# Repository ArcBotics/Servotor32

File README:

All hardware for Servotor32 is licensed under a Creative Commons Attribution ShareAlike 3.0 United States License.
The full terms of this license can be read at:
http://creativecommons.org/licenses/by-sa/3.0/

All software is licensed under the MIT License.
Permission is hereby granted, free of charge, to any person obtaining a copy of this software and associated documentation files (the "Software"), to deal in the Software without restriction, including without limitation the rights to use, copy, modify, merge, publish, distribute, sublicense, and/or sell copies of the Software, and to permit persons to whom the Software is furnished to do so, subject to the following conditions:

The above copyright notice and this permission notice shall be included in all copies or substantial portions of the Software.

THE SOFTWARE IS PROVIDED "AS IS", WITHOUT WARRANTY OF ANY KIND, EXPRESS OR IMPLIED, INCLUDING BUT NOT LIMITED TO THE WARRANTIES OF MERCHANTABILITY, FITNESS FOR A PARTICULAR PURPOSE AND NONINFRINGEMENT. IN NO EVENT SHALL THE AUTHORS OR COPYRIGHT HOLDERS BE LIABLE FOR ANY CLAIM, DAMAGES OR OTHER LIABILITY, WHETHER IN AN ACTION OF CONTRACT, TORT OR OTHERWISE, ARISING FROM, OUT OF OR IN CONNECTION WITH THE SOFTWARE OR THE USE OR OTHER DEALINGS IN THE SOFTWARE.

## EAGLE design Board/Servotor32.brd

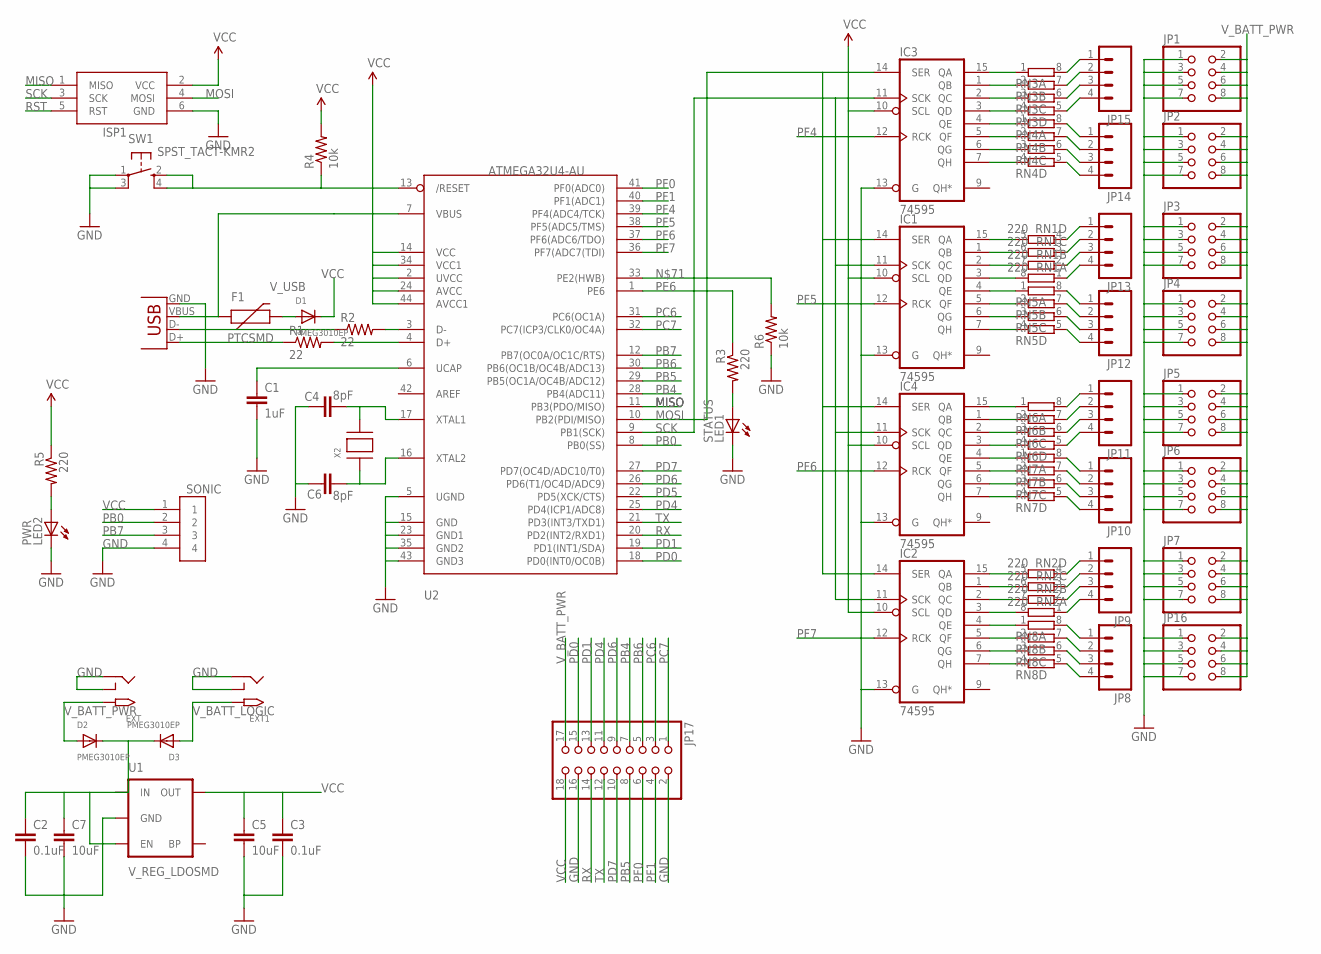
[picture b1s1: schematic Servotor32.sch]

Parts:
C1: 1uF; 0603-CAP
C2, C3: 0.1uF; 0603-CAP
C4, C6: 8pF; 0603-CAP
C5, C7: 10uF; 0805
D1, D2, D3: PMEG3010EP; SOD-128
EXT, EXT1: 2.1MMJACKTHM; PJ-102A
F1: PTCSMD; PTC-1206
IC1, IC2, IC3, IC4: 74595; TSSOP16
ISP1: AVRISP-6; AVRISP
JP1, JP2, JP3, JP4, JP5, JP6, JP7, JP16: PINHD-2X4; 2X04
JP8, JP9, JP10, JP11, JP12, JP13, JP14, JP15: M04PTH; 1X04
JP17: PINHD-2X9-BIG; 2X09-BIG
LED1: STATUS; SML0805
LED2: PWR; SML0805
R1, R2: 22; 0603-RES
R3, R5: 220; 0603-RES
R4, R6: 10k; 0603-RES
RN1, RN2: 220; EXB38V
RN3, RN4, RN5, RN6, RN7, RN8: 4R-NEXB38V; EXB38V
SONIC: SONIC; 1X04-BIG
SW1: SPST_TACT-KMR2; KMR2
U1: V_REG_LDOSMD; SOT23-5
U2: ATMEGA32U4-AU; TQFP44
X1: USBSMD; USB-MINIB
X2: XTALNX5032; NX5032

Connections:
D+: R1.2, U2.4 (D+)
D-: R2.2, U2.3 (D-)
GND: C1.2, C2.2, C3.2, C4.2, C5.2, C6.2, C7.2, EXT.RING, EXT.RING_SW, EXT1.RING, EXT1.RING_SW, IC1.8 (GND), IC1.13 (G), IC2.8 (GND), IC2.13 (G), IC3.8 (GND), IC3.13 (G), IC4.8 (GND), IC4.13 (G), ISP1.6 (GND), JP1.1, JP1.3, JP1.5, JP1.7, JP2.1, JP2.3, JP2.5, JP2.7, JP3.1, JP3.3, JP3.5, JP3.7, JP4.1, JP4.3, JP4.5, JP4.7, JP5.1, JP5.3, JP5.5, JP5.7, JP6.1, JP6.3, JP6.5, JP6.7, JP7.1, JP7.3, JP7.5, JP7.7, JP16.1, JP16.3, JP16.5, JP16.7, JP17.2, JP17.16, LED1.C, LED2.C, R6.1, SONIC.4, SW1.1, SW1.3 (P1), U1.2 (GND), U2.5 (UGND), U2.15 (GND), U2.23 (GND1), U2.35 (GND2), U2.43 (GND3), X1.GND
MISO: ISP1.1 (MISO), U2.11 (PB3(PDO/MISO))
MOSI: IC1.14 (SER), IC2.14 (SER), IC3.14 (SER), IC4.14 (SER), ISP1.4 (MOSI), U2.10 (PB2(PDI/MISO))
unnamed: IC3.15 (QA), RN3.1
unnamed: LED2.A, R5.2
unnamed: IC1.3 (QD), RN1.8 (2)
unnamed: R2.1, X1.D-
unnamed: R1.1, X1.D+
unnamed: IC2.3 (QD), RN2.8 (2)
unnamed: IC1.2 (QC), RN1.7 (2)
unnamed: IC2.2 (QC), RN2.7 (2)
unnamed: IC1.1 (QB), RN1.6 (2)
unnamed: IC3.1 (QB), RN3.2 (1)
unnamed: IC1.15 (QA), RN1.5 (2)
unnamed: IC3.2 (QC), RN3.3 (1)
unnamed: IC3.3 (QD), RN3.4 (1)
unnamed: IC2.1 (QB), RN2.6 (2)
unnamed: IC2.15 (QA), RN2.5 (2)
unnamed: IC3.4 (QE), RN4.1
unnamed: IC3.5 (QF), RN4.2 (1)
unnamed: IC3.6 (QG), RN4.3 (1)
unnamed: IC3.7 (QH), RN4.4 (1)
unnamed: IC1.4 (QE), RN5.1
unnamed: IC1.5 (QF), RN5.2 (1)
unnamed: JP13.1, RN1.4 (1)
unnamed: IC1.6 (QG), RN5.3 (1)
unnamed: IC1.7 (QH), RN5.4 (1)
unnamed: JP12.1, RN5.8 (2)
unnamed: JP13.2, RN1.3 (1)
unnamed: JP13.3, RN1.2 (1)
unnamed: JP13.4, RN1.1
unnamed: JP12.2, RN5.7 (2)
unnamed: JP12.3, RN5.6 (2)
unnamed: JP12.4, RN5.5 (2)
unnamed: JP15.1, RN3.8 (2)
unnamed: JP15.2, RN3.7 (2)
unnamed: JP15.3, RN3.6 (2)
unnamed: JP15.4, RN3.5 (2)
unnamed: JP14.1, RN4.8 (2)
unnamed: JP14.2, RN4.7 (2)
unnamed: JP14.3, RN4.6 (2)
unnamed: JP14.4, RN4.5 (2)
unnamed: JP9.4, RN2.1
unnamed: JP9.3, RN2.2 (1)
unnamed: JP9.2, RN2.3 (1)
unnamed: JP9.1, RN2.4 (1)
unnamed: IC2.4 (QE), RN8.1
unnamed: IC2.5 (QF), RN8.2 (1)
unnamed: IC2.6 (QG), RN8.3 (1)
unnamed: IC2.7 (QH), RN8.4 (1)
unnamed: JP8.1, RN8.8 (2)
unnamed: JP8.2, RN8.7 (2)
unnamed: JP8.3, RN8.6 (2)
unnamed: JP8.4, RN8.5 (2)
unnamed: IC4.1 (QB), RN6.2 (1)
unnamed: IC4.2 (QC), RN6.3 (1)
unnamed: IC4.3 (QD), RN6.4 (1)
unnamed: IC4.4 (QE), RN7.1
unnamed: IC4.5 (QF), RN7.2 (1)
unnamed: IC4.6 (QG), RN7.3 (1)
unnamed: IC4.7 (QH), RN7.4 (1)
unnamed: JP11.1, RN6.8 (2)
unnamed: JP11.2, RN6.7 (2)
unnamed: JP11.3, RN6.6 (2)
unnamed: JP11.4, RN6.5 (2)
unnamed: JP10.1, RN7.8 (2)
unnamed: JP10.2, RN7.7 (2)
unnamed: JP10.3, RN7.6 (2)
unnamed: JP10.4, RN7.5 (2)
unnamed: LED1.A, R3.2
unnamed: R6.2, U2.33 (PE2(HWB))
unnamed: IC4.15 (QA), RN6.1
PB0: SONIC.2, U2.8 (PB0(SS))
PB4: JP17.7, U2.28 (PB4(ADC11))
PB5: JP17.8, U2.29 (PB5(OC1A/OC4B/ADC12))
PB6: JP17.5, U2.30 (PB6(OC1B/OC4B/ADC13))
PB7: SONIC.3, U2.12 (PB7(OC0A/OC1C/RTS))
PC6: JP17.3, U2.31 (PC6(OC1A))
PC7: JP17.1, U2.32 (PC7(ICP3/CLK0/OC4A))
PD0: JP17.15, U2.18 (PD0(INT0/OC0B))
PD1: JP17.13, U2.19 (PD1(INT1/SDA))
PD4: JP17.11, U2.25 (PD4(ICP1/ADC8))
PD5: U2.22 (PD5(XCK/CTS))
PD6: JP17.9, U2.26 (PD6(T1/OC4D/ADC9))
PD7: JP17.10, U2.27 (PD7(OC4D/ADC10/T0))
PE6: R3.1, U2.1 (PE6)
PF0: JP17.6, U2.41 (PF0(ADC0))
PF1: JP17.4, U2.40 (PF1(ADC1))
PF4: IC3.12 (RCK), U2.39 (PF4(ADC4/TCK))
PF5: IC1.12 (RCK), U2.38 (PF5(ADC5/TMS))
PF6: IC4.12 (RCK), U2.37 (PF6(ADC6/TDO))
PF7: IC2.12 (RCK), U2.36 (PF7(ADC7(TDI))
RST: ISP1.5 (RST), R4.1, SW1.2 (S), SW1.4 (S1), U2.13 (/RESET)
RX: JP17.14, U2.20 (PD2(INT2/RXD1))
SCK: IC1.11 (SCK), IC2.11 (SCK), IC3.11 (SCK), IC4.11 (SCK), ISP1.3 (SCK), U2.9 (PB1(SCK))
TX: JP17.12, U2.21 (PD3(INT3/TXD1))
UCAP: C1.1, U2.6 (UCAP)
VBUS: F1.1, U2.7 (VBUS), X1.VBUS
VCC: C3.1, C5.1, D1.P$1 (C), IC1.10 (SCL), IC1.16 (VCC), IC2.10 (SCL), IC2.16 (VCC), IC3.10 (SCL), IC3.16 (VCC), IC4.10 (SCL), IC4.16 (VCC), ISP1.2 (VCC), JP17.18, R4.2, R5.1, SONIC.1, U1.5 (OUT), U2.2 (UVCC), U2.14 (VCC), U2.24 (AVCC), U2.34 (VCC1), U2.44 (AVCC1)
V_BATT: C2.1, C7.1, D2.P$1 (C), D3.P$1 (C), U1.1 (IN), U1.3 (EN)
V_BATT_LOGIC: D3.P$2 (A), EXT1.TIP
V_BATT_PWR: D2.P$2 (A), EXT.TIP, JP1.2, JP1.4, JP1.6, JP1.8, JP2.2, JP2.4, JP2.6, JP2.8, JP3.2, JP3.4, JP3.6, JP3.8, JP4.2, JP4.4, JP4.6, JP4.8, JP5.2, JP5.4, JP5.6, JP5.8, JP6.2, JP6.4, JP6.6, JP6.8, JP7.2, JP7.4, JP7.6, JP7.8, JP16.2, JP16.4, JP16.6, JP16.8, JP17.17
V_USB: D1.P$2 (A), F1.2
XTAL1: C4.1, U2.17 (XTAL1), X2.P$2
XTAL2: C6.1, U2.16 (XTAL2), X2.P$1

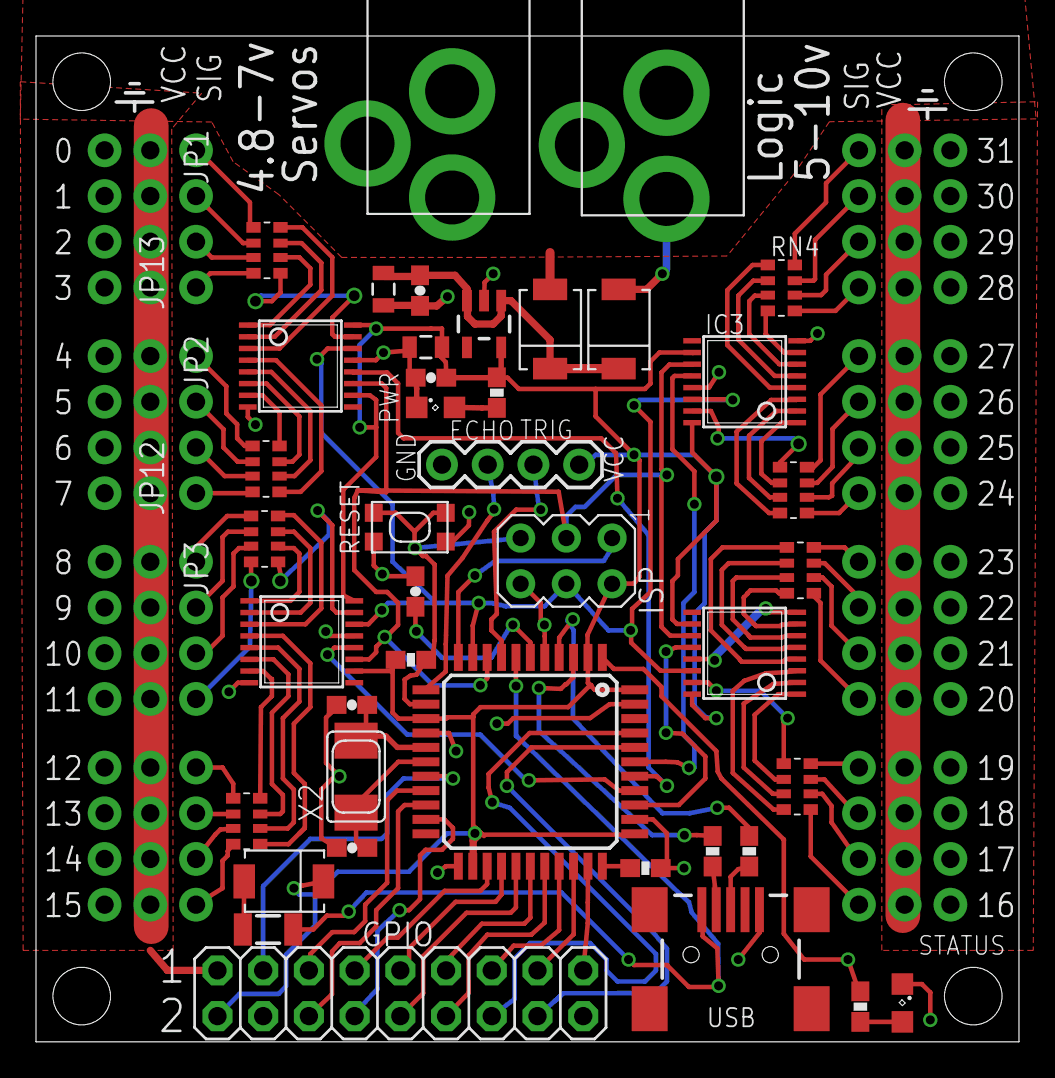
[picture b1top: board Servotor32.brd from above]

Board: 2 copper layers, 54.6 x 55.9 mm, 57 parts (0 on the bottom side), 106 nets.

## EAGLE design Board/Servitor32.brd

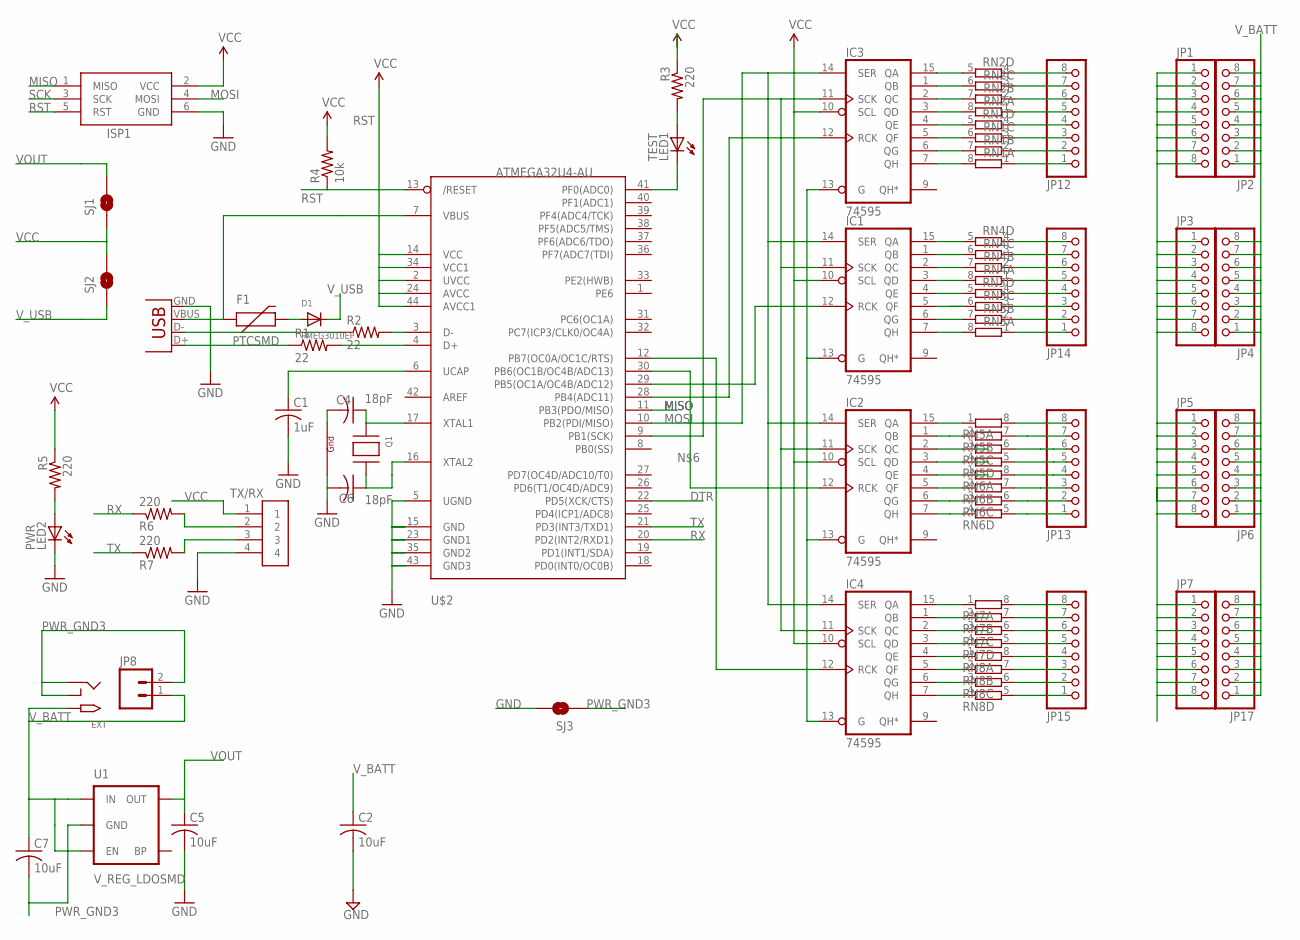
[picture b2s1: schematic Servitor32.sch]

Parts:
C1: 1uF; C0805K
C2, C5: 10uF; C0805K
C4, C6: 18pF; C0805K
C7: 10uF; C0805
D1: PMEG3010EP; SOD-128
EXT: 2.1MMJACKTHM; PJ-102A
F1: PTCSMD; PTC-1206
IC1, IC2, IC3, IC4: 74595; TSSOP16
ISP1: AVRISP-6; AVRISP
JP1, JP2, JP3, JP4, JP5, JP6, JP7, JP12, JP13, JP14, JP15, JP17: PINHD-1X8CLEANBIG; 1X08-CLEANBIG
JP8: M023.5MM; SCREWTERMINAL-3.5MM-2
LED1: TEST; SML0805
LED2: PWR; SML0805
Q1: XTAL-4-3225; NX3225
R1, R2: 22; R0805
R3, R5, R6, R7: 220; R0805
R4: 10k; R0805
RN1, RN2, RN3, RN4, RN5, RN6, RN7, RN8: 4R-NEXB38V; EXB38V
SJ1, SJ2, SJ3: SOLDERJUMPER-OLDTRACE; SJ_2S-TRACE
TX/RX: TX/RX; 1X04-BIG
U1: V_REG_LDOSMD; SOT23-5
U$2: ATMEGA32U4-AU; TQFP44
X1: USBSMD; USB-MINIB

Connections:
D+: R1.1, X1.D+
D-: R2.1, X1.D-
DTR: U$2.22 (PD5(XCK/CTS))
GND: C1.2, C5.2, C6.2, IC1.8 (GND), IC2.8 (GND), IC3.8 (GND), IC4.8 (GND), ISP1.6 (GND), LED2.C, Q1.4 (G2), SJ3.2, TX/RX.4, U$2.5 (UGND), U$2.15 (GND), U$2.23 (GND1), U$2.35 (GND2), U$2.43 (GND3), X1.GND
MISO: ISP1.1 (MISO), U$2.11 (PB3(PDO/MISO))
MOSI: IC1.14 (SER), IC2.14 (SER), IC3.14 (SER), IC4.14 (SER), ISP1.4 (MOSI), U$2.10 (PB2(PDI/MISO))
unnamed: IC3.15 (QA), RN2.5 (2)
unnamed: LED2.A, R5.2
unnamed: C4.1, Q1.1 (X1), U$2.17 (XTAL1)
unnamed: R2.2, U$2.3 (D-)
unnamed: R1.2, U$2.4 (D+)
unnamed: LED1.C, U$2.41 (PF0(ADC0))
unnamed: LED1.A, R3.2
unnamed: C4.2, Q1.2 (G1)
unnamed: C6.1, Q1.3 (X2), U$2.16 (XTAL2)
unnamed: D1.P$2 (A), F1.2
unnamed: IC3.1 (QB), RN2.6 (2)
unnamed: IC1.15 (QA), RN4.5 (2)
unnamed: IC3.2 (QC), RN2.7 (2)
unnamed: IC3.3 (QD), RN2.8 (2)
unnamed: C1.1, U$2.6 (UCAP)
unnamed: IC3.4 (QE), RN1.5 (2)
unnamed: IC3.5 (QF), RN1.6 (2)
unnamed: IC3.6 (QG), RN1.7 (2)
unnamed: IC3.7 (QH), RN1.8 (2)
unnamed: JP12.8, RN2.4 (1)
unnamed: JP12.7, RN2.3 (1)
unnamed: JP12.6, RN2.2 (1)
unnamed: JP12.5, RN2.1
unnamed: JP12.4, RN1.4 (1)
unnamed: JP12.3, RN1.3 (1)
unnamed: JP12.2, RN1.2 (1)
unnamed: IC1.1 (QB), RN4.6 (2)
unnamed: IC1.2 (QC), RN4.7 (2)
unnamed: IC1.3 (QD), RN4.8 (2)
unnamed: IC1.4 (QE), RN3.5 (2)
unnamed: IC1.5 (QF), RN3.6 (2)
unnamed: IC1.6 (QG), RN3.7 (2)
unnamed: IC1.7 (QH), RN3.8 (2)
unnamed: IC2.15 (QA), RN5.1
unnamed: IC2.1 (QB), RN5.2 (1)
unnamed: IC2.3 (QD), RN5.4 (1)
unnamed: IC2.4 (QE), RN6.1
unnamed: IC2.5 (QF), RN6.2 (1)
unnamed: IC2.6 (QG), RN6.3 (1)
unnamed: IC2.7 (QH), RN6.4 (1)
unnamed: IC4.7 (QH), RN8.4 (1)
unnamed: IC4.15 (QA), RN7.1
unnamed: IC4.2 (QC), RN7.3 (1)
unnamed: IC4.3 (QD), RN7.4 (1)
unnamed: IC4.4 (QE), RN8.1
unnamed: IC4.5 (QF), RN8.2 (1)
unnamed: IC4.6 (QG), RN8.3 (1)
unnamed: IC2.2 (QC), RN5.3 (1)
unnamed: IC4.1 (QB), RN7.2 (1)
unnamed: JP12.1, RN1.1
unnamed: JP14.8, RN4.4 (1)
unnamed: JP14.7, RN4.3 (1)
unnamed: JP14.6, RN4.2 (1)
unnamed: JP14.5, RN4.1
unnamed: JP14.4, RN3.4 (1)
unnamed: JP14.3, RN3.3 (1)
unnamed: JP14.2, RN3.2 (1)
unnamed: JP13.8, RN5.8 (2)
unnamed: JP13.7, RN5.7 (2)
unnamed: JP13.5, RN5.5 (2)
unnamed: JP13.4, RN6.8 (2)
unnamed: JP13.3, RN6.7 (2)
unnamed: JP13.2, RN6.6 (2)
unnamed: JP13.1, RN6.5 (2)
unnamed: JP15.1, RN8.5 (2)
unnamed: JP15.8, RN7.8 (2)
unnamed: JP15.6, RN7.6 (2)
unnamed: JP15.5, RN7.5 (2)
unnamed: JP15.4, RN8.8 (2)
unnamed: JP15.3, RN8.7 (2)
unnamed: JP15.2, RN8.6 (2)
unnamed: JP13.6, RN5.6 (2)
unnamed: JP15.7, RN7.7 (2)
unnamed: JP14.1, RN3.1
unnamed: R7.2, TX/RX.3
unnamed: R6.2, TX/RX.2
PB4: IC3.12 (RCK), U$2.28 (PB4(ADC11))
PB5: IC1.12 (RCK), U$2.29 (PB5(OC1A/OC4B/ADC12))
PB6: IC2.12 (RCK), U$2.30 (PB6(OC1B/OC4B/ADC13))
PB7: IC4.12 (RCK), U$2.12 (PB7(OC0A/OC1C/RTS))
PWR_GND3: C2.2, C7.2, EXT.RING, EXT.RING_SW, IC1.13 (G), IC2.13 (G), IC3.13 (G), IC4.13 (G), JP1.1, JP1.2, JP1.3, JP1.4, JP1.5, JP1.6, JP1.7, JP1.8, JP3.1, JP3.2, JP3.3, JP3.4, JP3.5, JP3.6, JP3.7, JP3.8, JP5.1, JP5.2, JP5.3, JP5.4, JP5.5, JP5.6, JP5.7, JP5.8, JP7.1, JP7.2, JP7.3, JP7.4, JP7.5, JP7.6, JP7.7, JP7.8, JP8.2, SJ3.1, U1.2 (GND)
RST: ISP1.5 (RST), R4.1, U$2.13 (/RESET)
RX: R6.1, U$2.20 (PD2(INT2/RXD1))
SCK: IC1.11 (SCK), IC2.11 (SCK), IC3.11 (SCK), IC4.11 (SCK), ISP1.3 (SCK), U$2.9 (PB1(SCK))
TX: R7.1, U$2.21 (PD3(INT3/TXD1))
VBUS: F1.1, U$2.7 (VBUS), X1.VBUS
VCC: IC1.10 (SCL), IC1.16 (VCC), IC2.10 (SCL), IC2.16 (VCC), IC3.10 (SCL), IC3.16 (VCC), IC4.10 (SCL), IC4.16 (VCC), ISP1.2 (VCC), R3.1, R4.2, R5.1, SJ1.1, SJ2.2, TX/RX.1, U$2.2 (UVCC), U$2.14 (VCC), U$2.24 (AVCC), U$2.34 (VCC1), U$2.44 (AVCC1)
VOUT: C5.1, SJ1.2, U1.5 (OUT)
V_BATT: C2.1, C7.1, EXT.TIP, JP2.1, JP2.2, JP2.3, JP2.4, JP2.5, JP2.6, JP2.7, JP2.8, JP4.1, JP4.2, JP4.3, JP4.4, JP4.5, JP4.6, JP4.7, JP4.8, JP6.1, JP6.2, JP6.3, JP6.4, JP6.5, JP6.6, JP6.7, JP6.8, JP8.1, JP17.1, JP17.2, JP17.3, JP17.4, JP17.5, JP17.6, JP17.7, JP17.8, U1.1 (IN), U1.3 (EN)
V_USB: D1.P$1 (C), SJ2.1

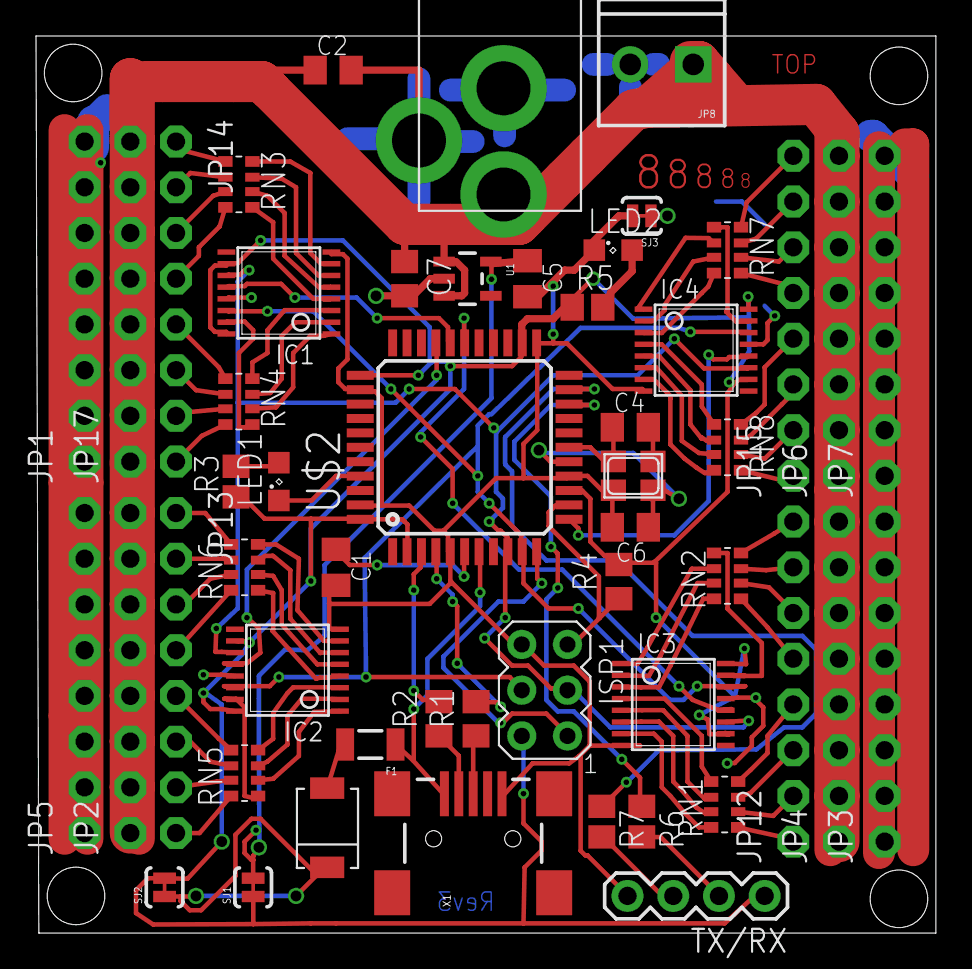
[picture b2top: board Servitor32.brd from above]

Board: 2 copper layers, 50.0 x 49.8 mm, 52 parts (0 on the bottom side), 95 nets.

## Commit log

2012-04-15 Rev 4
2012-10-02 Rev10 Update for Production
2012-10-26 Servotor32 1.4 firmware update
2012-10-26 Servotor32 Firmware 1.3 update
2012-10-26 removed old files
2012-10-26 added new fuse settings
2012-10-30 1.5 update, way less shaking, near-instant servo command handling
2012-11-08 fixed reset error with caterina bootloader, committed source files"
2012-12-25 Servotor 1.7 Update, stable servos
2013-01-10 Servotor 2.0 Update. Backend hiding, library-based, new change engine
2013-01-23 Used streams for Serial and Serial1 so print messages are common.
2013-02-03 addde CC-A-SA license
2013-02-03 addded MIT License to code
2013-04-02 Fixed include to have the correct casing.
    Fixed include to allow compiling the code on a case-sensitive filesystem.
2013-10-02 Create temp
2016-02-09 Included ability to toggle pins based on serial commands
2016-05-21 Updated library to Arduino 1.6 library specs

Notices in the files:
parts and their libraries:
SparkFun-Passives: Licensing: CC v3.0 Share-Alike You are welcome to use this library for commercial purposes.
